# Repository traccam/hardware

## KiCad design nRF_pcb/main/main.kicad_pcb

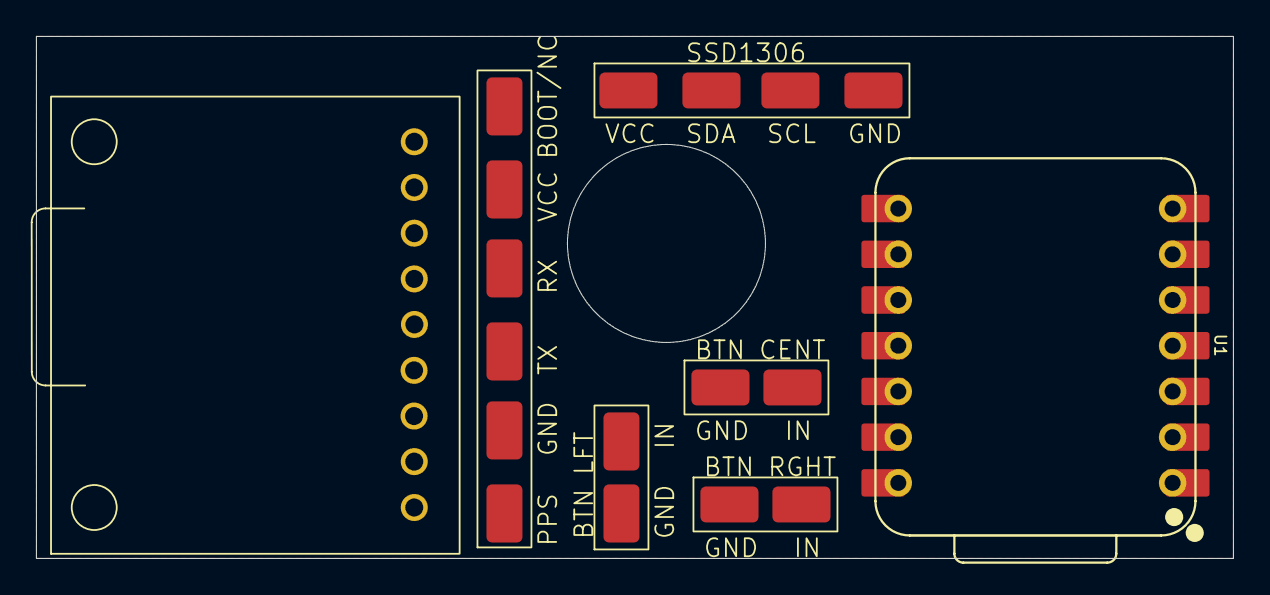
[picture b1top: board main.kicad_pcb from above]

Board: 2 copper layers, 66.5 x 29.0 mm, 7 parts (0 on the bottom side), 11 nets, no tracks yet.

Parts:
SW_CENTER1: SW_Push; Button Center
SW_LEFT1: SW_Push; Button Left
SW_RIGHT1: SW_Push; Button Right
U1: XIAO-nRF52840-SMD; XIAO-nRF52840-DIP
U2: SSD1306
U4: BE-280; BE-280 GPS
U5: SD Breakout; Adafruit SD Breakout

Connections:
+3.3V: U1.12 (3V3), U2.14 (VCC), U4.5 (VCC), U5.1 (3V)
/GPS_PPS: U1.2 (P0.03_A1_D1), U4.1 (PPS)
/GPS_RX: U1.7 (P1.11_D6_TX), U4.4 (RX_UART)
/GPS_TX: U1.8 (P1.12_D7_RX), U4.3 (TX_UART)
/SD_CS: U1.4 (P0.29_A3_D3), U5.6 (D3/CS)
/SD_MISO: U1.10 (P1.14_D9_MISO), U5.4 (D0/SO)
/SD_MOSI: U1.11 (P1.15_D10_MOSI), U5.5 (CMD/SI)
GND: SW_LEFT1.1, SW_RIGHT1.1, U1.13 (GND), U2.7 (VSS), U4.2 (GND), U5.2 (GND)
unnamed: U1.5 (P0.04_A4_D4_SDA), U2.11 (SDA)
unnamed: U1.6 (P0.05_A5_D5_SCL), U2.10 (SCL)
unnamed: U1.9 (P1.13_D8_SCK), U5.3 (CLK)

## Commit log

2026-02-26 init commit
2026-02-26 Add kicad WIP
2026-03-02 Refactor wires to labels
2026-03-02 Update PCB
2026-03-03 Refactor to 3.3V only architecture
2026-03-04 Implement adafruit sd board footprint
2026-03-13 Add 3V3 rail toggle
